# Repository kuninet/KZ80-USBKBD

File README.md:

# KZ80マイコン用 MSX USBキーボードアダプタ # 

## 概要 ##
* USBキーボードをRaspberry PI PICOにつなぎ、MSX互換のPPI(8255)へつなげるボードです。
  * HRA!氏のusb_keyboard_bridge_for_msxを使わせていただいています。

## 回路図

* [回路図(PDF)](https://github.com/kuninet/KZ80-USBKBD/blob/main/KiCAD/KZ80-USBKBD.pdf)

## 注意

* KiCADデータは [KiCAD](KiCAD)ディレクトリに入ってます。KiCad6を使用しています。KiCad v5以前では開けません。
* 基板製造データは[KiCAD/PCB](KiCAD/PCB)に入っています。
* ファームウェアの書き込みにはコツがいりますので、こちらのBLOG記事を参考にしてください。
  * [KZ80-USBKBD用 RaspberryPi Picoオブジェクトビルド方法](https://kuninet.org/2023/03/30/kz80-usbkbd%e7%94%a8-raspberrypi-pico%e3%82%aa%e3%83%96%e3%82%b8%e3%82%a7%e3%82%af%e3%83%88%e3%83%93%e3%83%ab%e3%83%89%e6%96%b9%e6%b3%95/)

## ライセンスについて
* 私が作成した回路についてはMITライセンスで公開します。

## 参考・使用させていただいた情報
* usb_keyboard_bridge_for_msx
  * https://github.com/hra1129/msx_tools/tree/main/usb_keyboard_bridge_for_msx
* Raspberry Pi Pico シンボル&フットプリント
  * https://datasheets.raspberrypi.org/rp2040/VGA-KiCAD.zip

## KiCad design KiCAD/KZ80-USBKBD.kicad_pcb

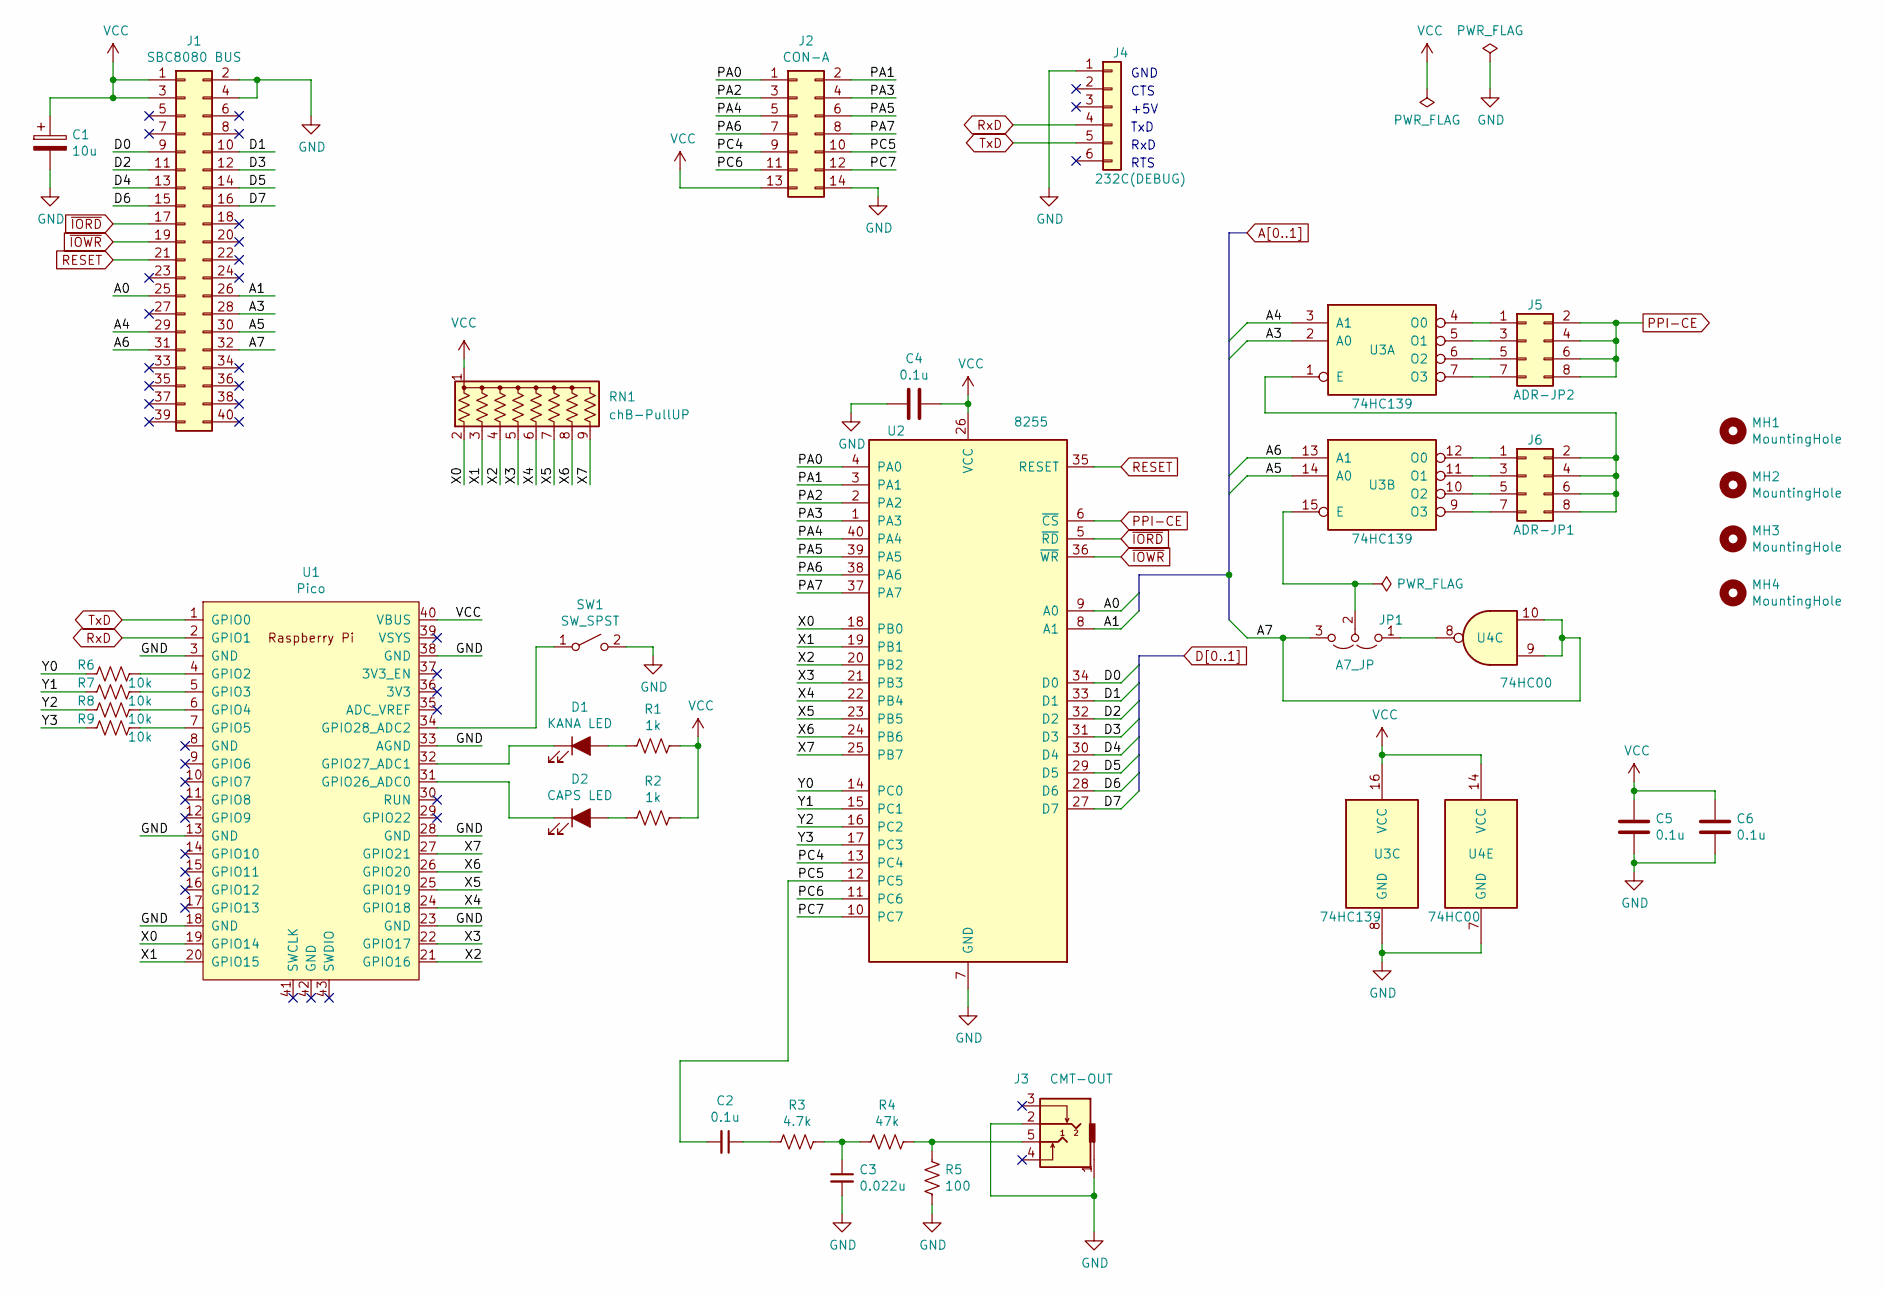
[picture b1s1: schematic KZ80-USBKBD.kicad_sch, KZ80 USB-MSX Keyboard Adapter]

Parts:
C1: 10u; CP_Radial_D5.0mm_P2.50mm
C2, C4, C5, C6: 0.1u; C_Disc_D3.0mm_W1.6mm_P2.50mm
C3: 0.022u; C_Disc_D3.0mm_W1.6mm_P2.50mm
D1: KANA LED; LED_D3.0mm
D2: CAPS LED; LED_D3.0mm
J1: SBC8080 BUS; PinHeader_2x20_P2.54mm_Horizontal
J2: CON-A; PinHeader_2x07_P2.54mm_Vertical
J3: CMT-OUT; AJ-1780
J4: 232C(DEBUG); PinHeader_1x06_P2.54mm_Horizontal
J5: ADR-JP2; PinHeader_2x04_P2.54mm_Vertical
J6: ADR-JP1; PinHeader_2x04_P2.54mm_Vertical
JP1: A7_JP; PinHeader_1x03_P2.54mm_Vertical
MH1, MH2, MH3, MH4: MountingHole; MountingHole_3.2mm_M3
R1, R2: 1k; R_Axial_DIN0207_L6.3mm_D2.5mm_P10.16mm_Horizontal
R3: 4.7k; R_Axial_DIN0207_L6.3mm_D2.5mm_P10.16mm_Horizontal
R4: 47k; R_Axial_DIN0207_L6.3mm_D2.5mm_P10.16mm_Horizontal
R5: 100; R_Axial_DIN0207_L6.3mm_D2.5mm_P10.16mm_Horizontal
R6, R7, R8, R9: 10k; R_Axial_DIN0207_L6.3mm_D2.5mm_P10.16mm_Horizontal
RN1: chB-PullUP; R_Array_SIP9
SW1: SW_SPST; PinHeader_1x03_P2.54mm_Vertical
U1: Pico; RPi_Pico_SMD_TH
U2: 8255; DIP-40_W15.24mm_Socket
U3: 74HC139
U4: 74HC00; DIP-14_W7.62mm_Socket

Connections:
/A3: J1.28, U3.2 (A0)
/A4: J1.29, U3.3 (A1)
/A5: J1.30, U3.14 (A0)
/A6: J1.31, U3.13 (A1)
/A7: J1.32, JP1.3 (B), U4.9, U4.10
/D2: J1.11, U2.32 (D2)
/D3: J1.12, U2.31 (D3)
/D4: J1.13, U2.30 (D4)
/D5: J1.14, U2.29 (D5)
/D6: J1.15, U2.28 (D6)
/D7: J1.16, U2.27 (D7)
/PA0: J2.1, U2.4 (PA0)
/PA1: J2.2, U2.3 (PA1)
/PA2: J2.3, U2.2 (PA2)
/PA3: J2.4, U2.1 (PA3)
/PA4: J2.5, U2.40 (PA4)
/PA5: J2.6, U2.39 (PA5)
/PA6: J2.7, U2.38 (PA6)
/PA7: J2.8, U2.37 (PA7)
/PC4: J2.9, U2.13 (PC4)
/PC5: C2.2, J2.10, U2.12 (PC5)
/PC6: J2.11, U2.11 (PC6)
/PC7: J2.12, U2.10 (PC7)
/X0: RN1.2 (R1), U1.19 (GPIO14), U2.18 (PB0)
/X1: RN1.3 (R2), U1.20 (GPIO15), U2.19 (PB1)
/X2: RN1.4 (R3), U1.21 (GPIO16), U2.20 (PB2)
/X3: RN1.5 (R4), U1.22 (GPIO17), U2.21 (PB3)
/X4: RN1.6 (R5), U1.24 (GPIO18), U2.22 (PB4)
/X5: RN1.7 (R6), U1.25 (GPIO19), U2.23 (PB5)
/X6: RN1.8 (R7), U1.26 (GPIO20), U2.24 (PB6)
/X7: RN1.9 (R8), U1.27 (GPIO21), U2.25 (PB7)
/Y0: R6.2, U2.14 (PC0)
/Y1: R7.2, U2.15 (PC1)
/Y2: R8.2, U2.16 (PC2)
/Y3: R9.2, U2.17 (PC3)
A0: J1.25, U2.9 (A0)
A1: J1.26, U2.8 (A1)
D0: J1.9, U2.34 (D0)
D1: J1.10, U2.33 (D1)
GND: C1.2, C3.2, C4.1, C5.2, C6.2, J1.2, J1.4, J2.14, J3.1, J3.2, J4.1, R5.2, SW1.2 (B), U1.3 (GND), U1.13 (GND), U1.18 (GND), U1.23 (GND), U1.28 (GND), U1.33 (AGND), U1.38 (GND), U2.7 (GND), U3.8 (GND), U4.7 (GND)
unnamed: C2.1, R3.2
unnamed: C3.1, R3.1, R4.2
unnamed: D1.1 (K), U1.32 (GPIO27_ADC1)
unnamed: D1.2 (A), R1.2
unnamed: D2.1 (K), U1.31 (GPIO26_ADC0)
unnamed: D2.2 (A), R2.2
unnamed: J3.5, R4.1, R5.1
unnamed: J5.1, U3.4 (O0)
unnamed: J5.3, U3.5 (O1)
unnamed: J5.5, U3.6 (O2)
unnamed: J5.7, U3.7 (O3)
unnamed: J6.1, U3.12 (O0)
unnamed: J6.2, J6.4, J6.6, J6.8, U3.1 (E)
unnamed: J6.3, U3.11 (O1)
unnamed: J6.5, U3.10 (O2)
unnamed: J6.7, U3.9 (O3)
unnamed: JP1.1 (A), U4.8
unnamed: JP1.2 (C), U3.15 (E)
unnamed: R6.1, U1.4 (GPIO2)
unnamed: R7.1, U1.5 (GPIO3)
unnamed: R8.1, U1.6 (GPIO4)
unnamed: R9.1, U1.7 (GPIO5)
unnamed: SW1.1 (A), U1.34 (GPIO28_ADC2)
PPI-CE: J5.2, J5.4, J5.6, J5.8, U2.6 (~CS)
RESET: J1.21, U2.35 (RESET)
RxD: J4.4, U1.2 (GPIO1)
TxD: J4.5, U1.1 (GPIO0)
VCC: C1.1, C4.2, C5.1, C6.1, J1.1, J1.3, J2.13, R1.1, R2.1, RN1.1 (common), U1.40 (VBUS), U2.26 (VCC), U3.16 (VCC), U4.14 (VCC)
~IORD: J1.17, U2.5 (~RD)
~IOWR: J1.19, U2.36 (~WR)

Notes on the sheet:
CTS
+5V
GND
RTS
RxD
TxD

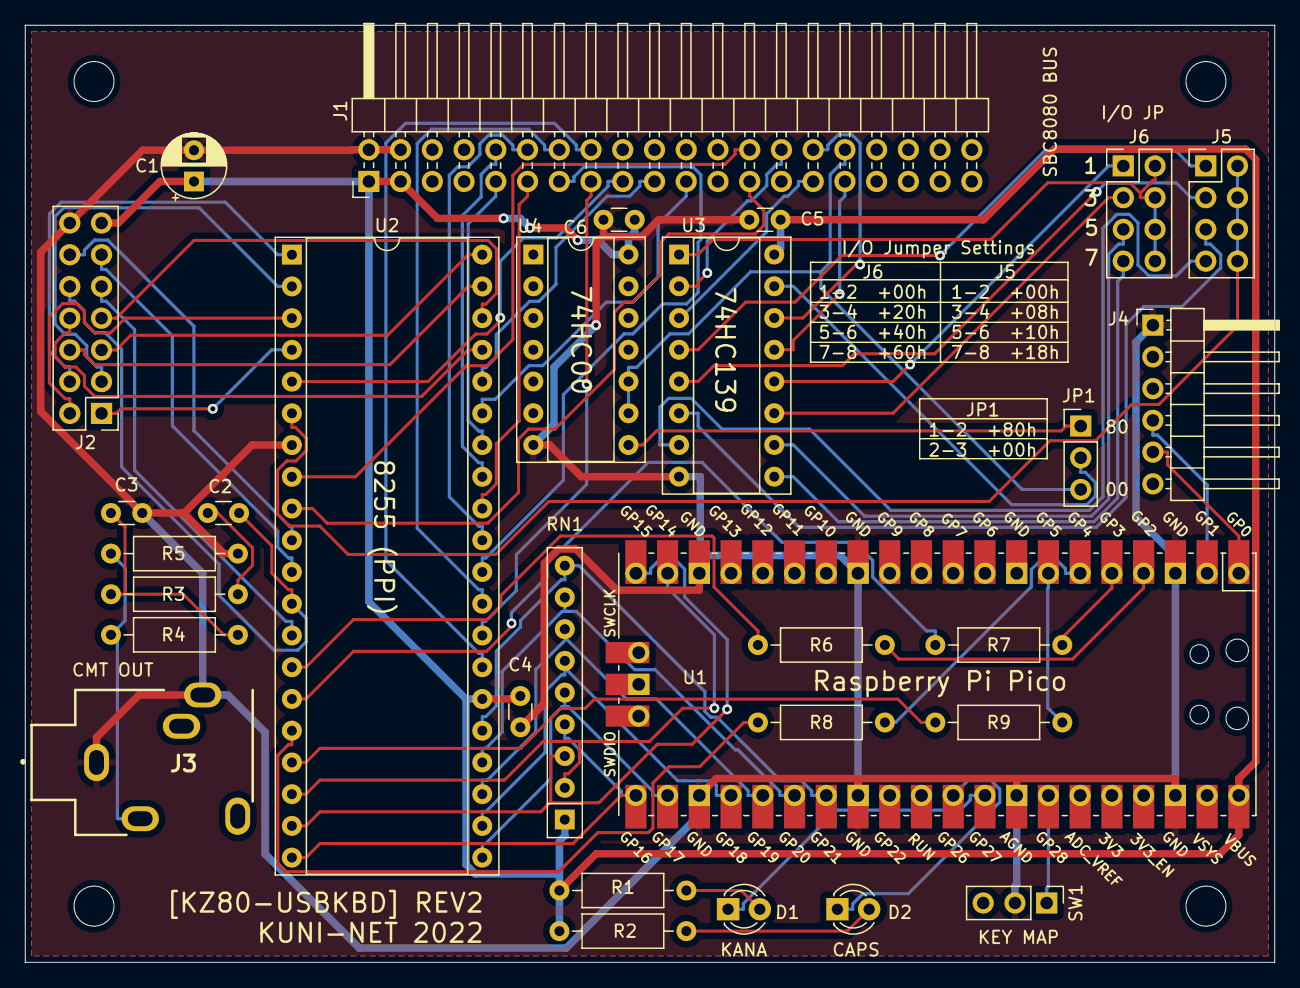
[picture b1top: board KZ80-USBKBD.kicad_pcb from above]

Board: 2 copper layers, 100.0 x 75.0 mm, 34 parts (0 on the bottom side), 70 nets.

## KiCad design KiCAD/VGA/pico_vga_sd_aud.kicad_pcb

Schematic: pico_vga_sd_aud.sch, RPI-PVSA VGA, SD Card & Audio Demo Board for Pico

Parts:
C1, C2: 1u; C_0603_1608Metric
C3, C10, C16, C19: 10u; C_0603_1608Metric
C4, C5, C6, C7, C8, C12, C13: 100n; C_0402_1005Metric
C9, C11: 2.2u; C_0603_1608Metric
C14, C15, C21: 47u; C_0805_2012Metric
C17, C18: 2.2n; C_0402_1005Metric
D1: MBR120; MBR120_SOD-123
H1, H2, H3, H4: MountingHole; MountingHole_2.7mm_M2.5
J1, J2: AudioJack3; CUI_SJ-3523-audio-jack
J3: Micro_SD_Card; microSD_HC_Molex_104031-0811
J4: L77HDE15SD1CH4F; DSUB-15-L77HDE15SD1CH4F
J5: USB_B_Micro; USB_Micro-B_Amphenol_10103594-0001LF_Horizontal_modified
J6: Conn_01x02; PinHeader_1x02_P2.54mm_Vertical
J7: Conn_02x03_Odd_Even; PinHeader_2x04_P2.54mm_Vertical
R1, R2: 220; R_0402_1005Metric
R3, R4: 100; R_0402_1005Metric
R5, R6: 470; R_0402_1005Metric
R7, R8: 1.8K; R_0402_1005Metric
R9: DNF; R_0402_1005Metric
R10, R11: 47; R_0402_1005Metric
R20, R21, R22, R27, R32, R37: 1k; R_0402_1005Metric
R23, R24: 10k; R_0402_1005Metric
R26, R31, R36: 499; R_0402_1005Metric
R28, R33, R38: 2k; R_0402_1005Metric
R29, R34, R39: 4.02k; R_0402_1005Metric
R30, R35, R40: 8.06k; R_0402_1005Metric
SW1, SW2, SW3, SW4: SW_Push; SW_Push_1P1T_NO_Vertical_Wuerth_434133025816
U1: TLV70033_SOT23-5; SOT-23-5
U2: Pico; RPi_Pico_SMD_TH
U3: NC7WZ16P6X; SOT-363_SC-70-6
U4: PCM5101A; TSSOP-20_4.4x6.5mm_P0.65mm

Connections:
+5V: C21.2, D1.2, J5.1, J6.2
/GPIO0: R20.1, R30.2, U2.1 (GPIO0)
/GPIO1: R29.2, U2.2 (GPIO1)
/GPIO2: R28.2, U2.4 (GPIO2)
/GPIO3: R27.2, U2.5 (GPIO3)
/GPIO4: R26.2, U2.6 (GPIO4)
/GPIO5: J3.5, R9.2, U2.7 (GPIO5)
/GPIO6: R21.1, R35.2, U2.9 (GPIO6)
/GPIO7: R34.2, U2.10 (GPIO7)
/GPIO8: R33.2, U2.11 (GPIO8)
/GPIO9: R32.2, U2.12 (GPIO9)
/GPIO10: R31.2, U2.14 (GPIO10)
/GPIO11: R22.1, R40.2, U2.15 (GPIO11)
/GPIO12: R39.2, U2.16 (GPIO12)
/GPIO13: R38.2, U2.17 (GPIO13)
/GPIO14: R37.2, U2.19 (GPIO14)
/GPIO15: R36.2, U2.20 (GPIO15)
/GPIO16: R11.2, U2.21 (GPIO16)
/GPIO17: R10.2, U2.22 (GPIO17)
/GPIO18: J3.3, U2.24 (GPIO18)
/GPIO19: J3.7, U2.25 (GPIO19)
/GPIO20: J7.3, U2.26 (GPIO20)
/GPIO21: J7.1, U2.27 (GPIO21)
/GPIO22: J3.2, U2.29 (GPIO22)
/GPIO26: U2.31 (GPIO26_ADC0), U4.14
/GPIO27: U2.32 (GPIO27_ADC1), U3.3, U4.13
/GPIO28: U2.34 (GPIO28_ADC2), U3.1, U4.15
/HSYNC: J4.13, R11.1
/PCM_AUDIO_L: C18.1, J1.2, R5.1
/PCM_AUDIO_R: C17.1, J1.3, R6.1
/PCM_L: R5.2, U4.6
/PCM_R: R6.2, U4.7
/PWM_AUDIO_L: C14.1, J2.2, R7.2
/PWM_AUDIO_R: C15.1, J2.3, R8.2
/PWM_L: R1.2, U3.6
/PWM_LL: C7.1, C14.2, R1.1, R3.2
/PWM_R: R2.2, U3.4
/PWM_RR: C8.1, C15.2, R2.1, R4.2
/RUN: SW1.1, U2.30 (RUN)
/SD_DAT1: J3.8, J7.4, R24.1
/SD_DAT2: J3.1, J7.2, R23.1
/SWCLK: J7.6, U2.41 (SWCLK)
/SWDIO: J7.5, U2.43 (SWDIO)
/VGA_B: J4.3, R36.1, R37.1, R38.1, R39.1, R40.1
/VGA_G: J4.2, R31.1, R32.1, R33.1, R34.1, R35.1
/VGA_R: J4.1, R26.1, R27.1, R28.1, R29.1, R30.1
/VSYNC: J4.14, R10.1
/VSYS: C1.1, D1.1, U1.1, U1.3, U2.39 (VSYS)
GND: C1.2, C2.2, C3.2, C4.2, C5.2, C6.2, C7.2, C8.2, C9.2, C10.2, C12.2, C13.2, C16.2, C17.2, C18.2, C19.2, C21.1, J1.1, J2.1, J3.6, J3.11, J4.0, J4.5, J4.6, J4.7, J4.8, J4.10, J5.5, J5.6, J7.7, J7.8, R3.1, R4.1, R7.1, R8.1, R9.1, SW1.2, U1.2, U2.3 (GND), U2.8 (GND), U2.13 (GND), U2.18 (GND), U2.23 (GND), U2.28 (GND), U2.33 (AGND), U2.38 (GND), U2.42 (GND), U3.2, U4.3, U4.9, U4.10, U4.11, U4.12, U4.16, U4.19
unnamed: C9.1, U4.5
unnamed: C11.1, U4.2
unnamed: C11.2, U4.4
unnamed: C13.1, U4.18
unnamed: R20.2, SW2.2
unnamed: R21.2, SW3.2
unnamed: R22.2, SW4.2
VBUS: J6.1, U2.40 (VBUS)

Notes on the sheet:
Pico
Audio Power
I2S/PCM Audio
PWM Audio
Micro SD Card
VGA
Connect 5V to VBUS if Pico is using USB Host mode
5V Power In
Power Options: 1) Connect J5 to 5V uUSB power supply. This provides power for this board & Pico, via diode D1 to VSYS. 2) Connect uUSB power supply to Pico directly. VSYS will then power this board. N.B. If USB Host functionality is required on Pico, then use option 1, and also fit Jumper J6 to pro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
VGA 'DAC'
Button A
Button B
Button C
SD_CLK
SD_CMD
SD_DAT0
SD_DAT1
SD_DAT2
SD_DAT3
DIN
BCK_PWM1
LRCLK_PWM0
RED_0
RED_1
RED_2
RED_3
RED_4
GREEN_0
GREEN_1
GREEN_2
GREEN_3
GREEN_4
BLUE_0
BLUE_1
BLUE_2
BLUE_3
BLUE_4
UART1_TX
UART1_RX
UART / 4-bit SD Selector & Debug

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
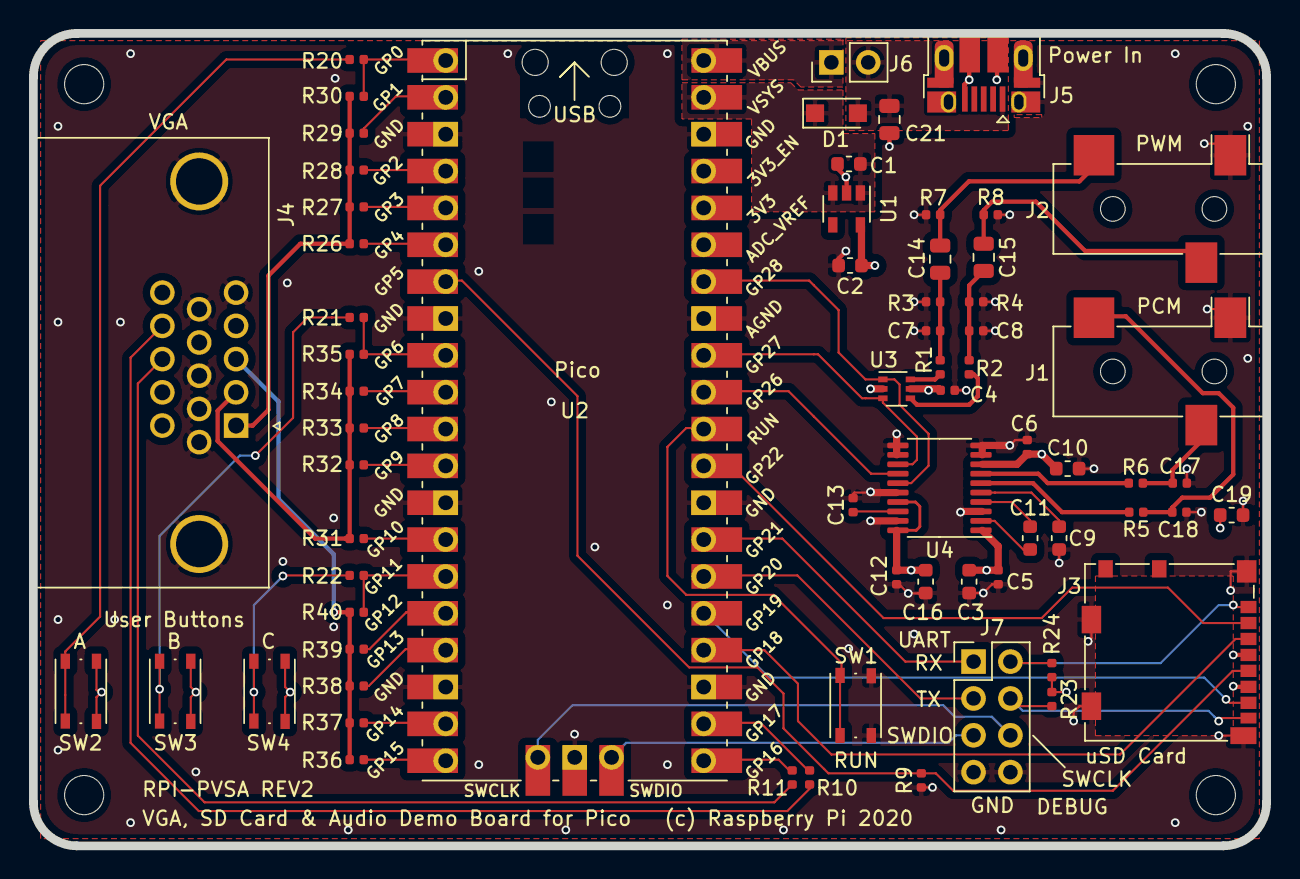
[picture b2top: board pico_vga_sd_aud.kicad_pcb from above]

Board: 4 copper layers, 85.0 x 56.0 mm, 71 parts (0 on the bottom side), 59 nets.

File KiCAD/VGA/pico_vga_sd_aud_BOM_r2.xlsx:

RPI-PVAS pico_vga_sd_aud BOM Rev2
17/079/2020
Reference designators | Quantity | Manufacturer Part Number (MPN) | Manufacturer | Description | Value
C1, C2 | 2 | GCM188R71C105KA64J | Murata | CAP CER 1UF 16V X7R 0603 | 1u
C9, C11 | 2 | GRM188R71A225KE15D | Murata | CAP CER 2.2UF 10V X7R 0603 | 2.2u
C3, C10, C16, C19 | 4 | GRM188R61A106KE69J | Murata | CAP CER 10UF 10V X5R 0603 | 10u
C4, C5, C6, C7, C8, C12, C13 | 7 | GRM155R71E104KE14J | Murata | CAP CER 0.1UF 25V X7R 0402 | 100n
C14, C15, C21 | 3 | GRM219R60J476ME44D | Murata | CAP CER 47UF 6.3V X5R 0805 | 47u
C17, C18 | 2 | GRM155R71H222KA01D | Murata | CAP CER 2200PF 50V X7R 0402 | 2.2n
D1 | 1 | MBR120VLSFT1G | ON Semiconductor | DIODE SCHOTTKY 20V 1A SOD123FL | MBR120VLSFT1G
J1, J2 | 2 | SJ-3523-SMT-TR | CUI Devices | CONN JACK STEREO 3.5MM SMD R/A | SJ-3523-SMT
J3 | 1 | 104031-0811 | Molex | CONN MICRO SD CARD PUSH-PULL R/A | 104031-0811
J4 | 1 | L77HDE15SD1CH4F | Amphenol ICC (Commercial Products) | CONN DSUB HD RCPT 15POS R/A SLDR | L77HDE15SD1CH4F
J5 | 1 | 10103594-0001LF | Amphenol ICC (FCI) | CONN RCPT USB2.0 MICRO B SMD R/A | 10103594-0001LF
J6 | 1 | TSW-102-23-T-S | Samtec Inc. | CONN HEADER VERT 2POS 2.54MM | TSW-102-23-T-S
J7 | 1 | 67997-208HLF | Amphenol ICC (FCI) | CONN HEADER VERT 8POS 2.54MM | 67997-208HLF
R1, R2 | 2 | RC0402FR-07220RL | Yageo | RES SMD 220 OHM 1% 1/16W 0402 | 220
R3, R4 | 2 | RC0402FR-07100RL | Yageo | RES SMD 100 OHM 1% 1/16W 0402 | 100
R5, R6 | 2 | RC0402FR-07470RP | Yageo | RES SMD 470 OHM 1% 1/16W 0402 | 470
R7, R8 | 2 | RC0402FR-071K8L | Yageo | RES SMD 1.8K OHM 1% 1/16W 0402 | 1.8K
R10, R11 | 2 | RC0402FR-0747RL | Yageo | RES SMD 47 OHM 1% 1/16W 0402 | 47
R20, R21, R22, R27, R32, R37 | 6 | RC0402FR-071KP | Yageo | RES SMD 1K OHM 1% 1/16W 0402 | 1k
R23, R24 | 2 | RC0402FR-0710KP | Yageo | RES SMD 10K OHM 1% 1/16W 0402 | 10k
R26, R31, R36 | 3 | RC0402FR-07499RL | Yageo | RES SMD 499 OHM 1% 1/16W 0402 | 499
R28, R33, R38 | 3 | RC0402FR-072KL | Yageo | RES SMD 2K OHM 1% 1/16W 0402 | 2k
R29, R34, R39 | 3 | RC0402FR-074K02L | Yageo | RES SMD 4.02K OHM 1% 1/16W 0402 | 4.02k
R30, R35, R40 | 3 | RC0402FR-078K06L | Yageo | RES SMD 8.06K OHM 1% 1/16W 0402 | 8.06k
SW1, SW2, SW3, SW4 | 4 | 434133025816 | Würth Elektronik | TACT SWITCH 4.2X3.2MM VERTICAL T | 434133025816
U1 | 1 | TLV70033DDCR | Texas Instruments | IC REG LINEAR 3.3V 200MA SOT23-5 | TLV70033DDCR
U3 | 1 | NC7WZ16P6X | ON Semiconductor | IC BUF NON-INVERT 5.5V SC70-6 | NC7WZ16P6X
U4 | 1 | PCM5101APWR | Texas Instruments | IC DAC 16/24/32BIT 384K 20TSSOP | PCM5101APWR

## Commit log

2021-08-08 init
2021-08-08 README 更新
2021-08-08 README更新 2
2021-08-08 基板製造ファイル移動
2021-08-08 プリントパターン最新化
2021-08-08 ガーバーファイル整理
2021-08-08 LEDフットプリント間違い修正
2021-08-08 回路図 PDF出力
2021-12-18 各種最新化
2022-01-17 REV1基板バグ対応、REV2作成、ガーバー出力
2022-06-01 REV2 基板 回路不足部分追加・パターン修正・ガーバー再出力
2024-04-28 部品表追加
